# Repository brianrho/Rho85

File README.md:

# Rho85
An Intel 8085 microprocessor trainer

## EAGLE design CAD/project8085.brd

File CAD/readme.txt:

This contains the Eagle .brd and .sch files, as well as PNG images of the schematic and PCB design. 
The schematic has been modified to correct the issues discovered during testing but the PCB design 
is still flawed; yet to be re-routed.

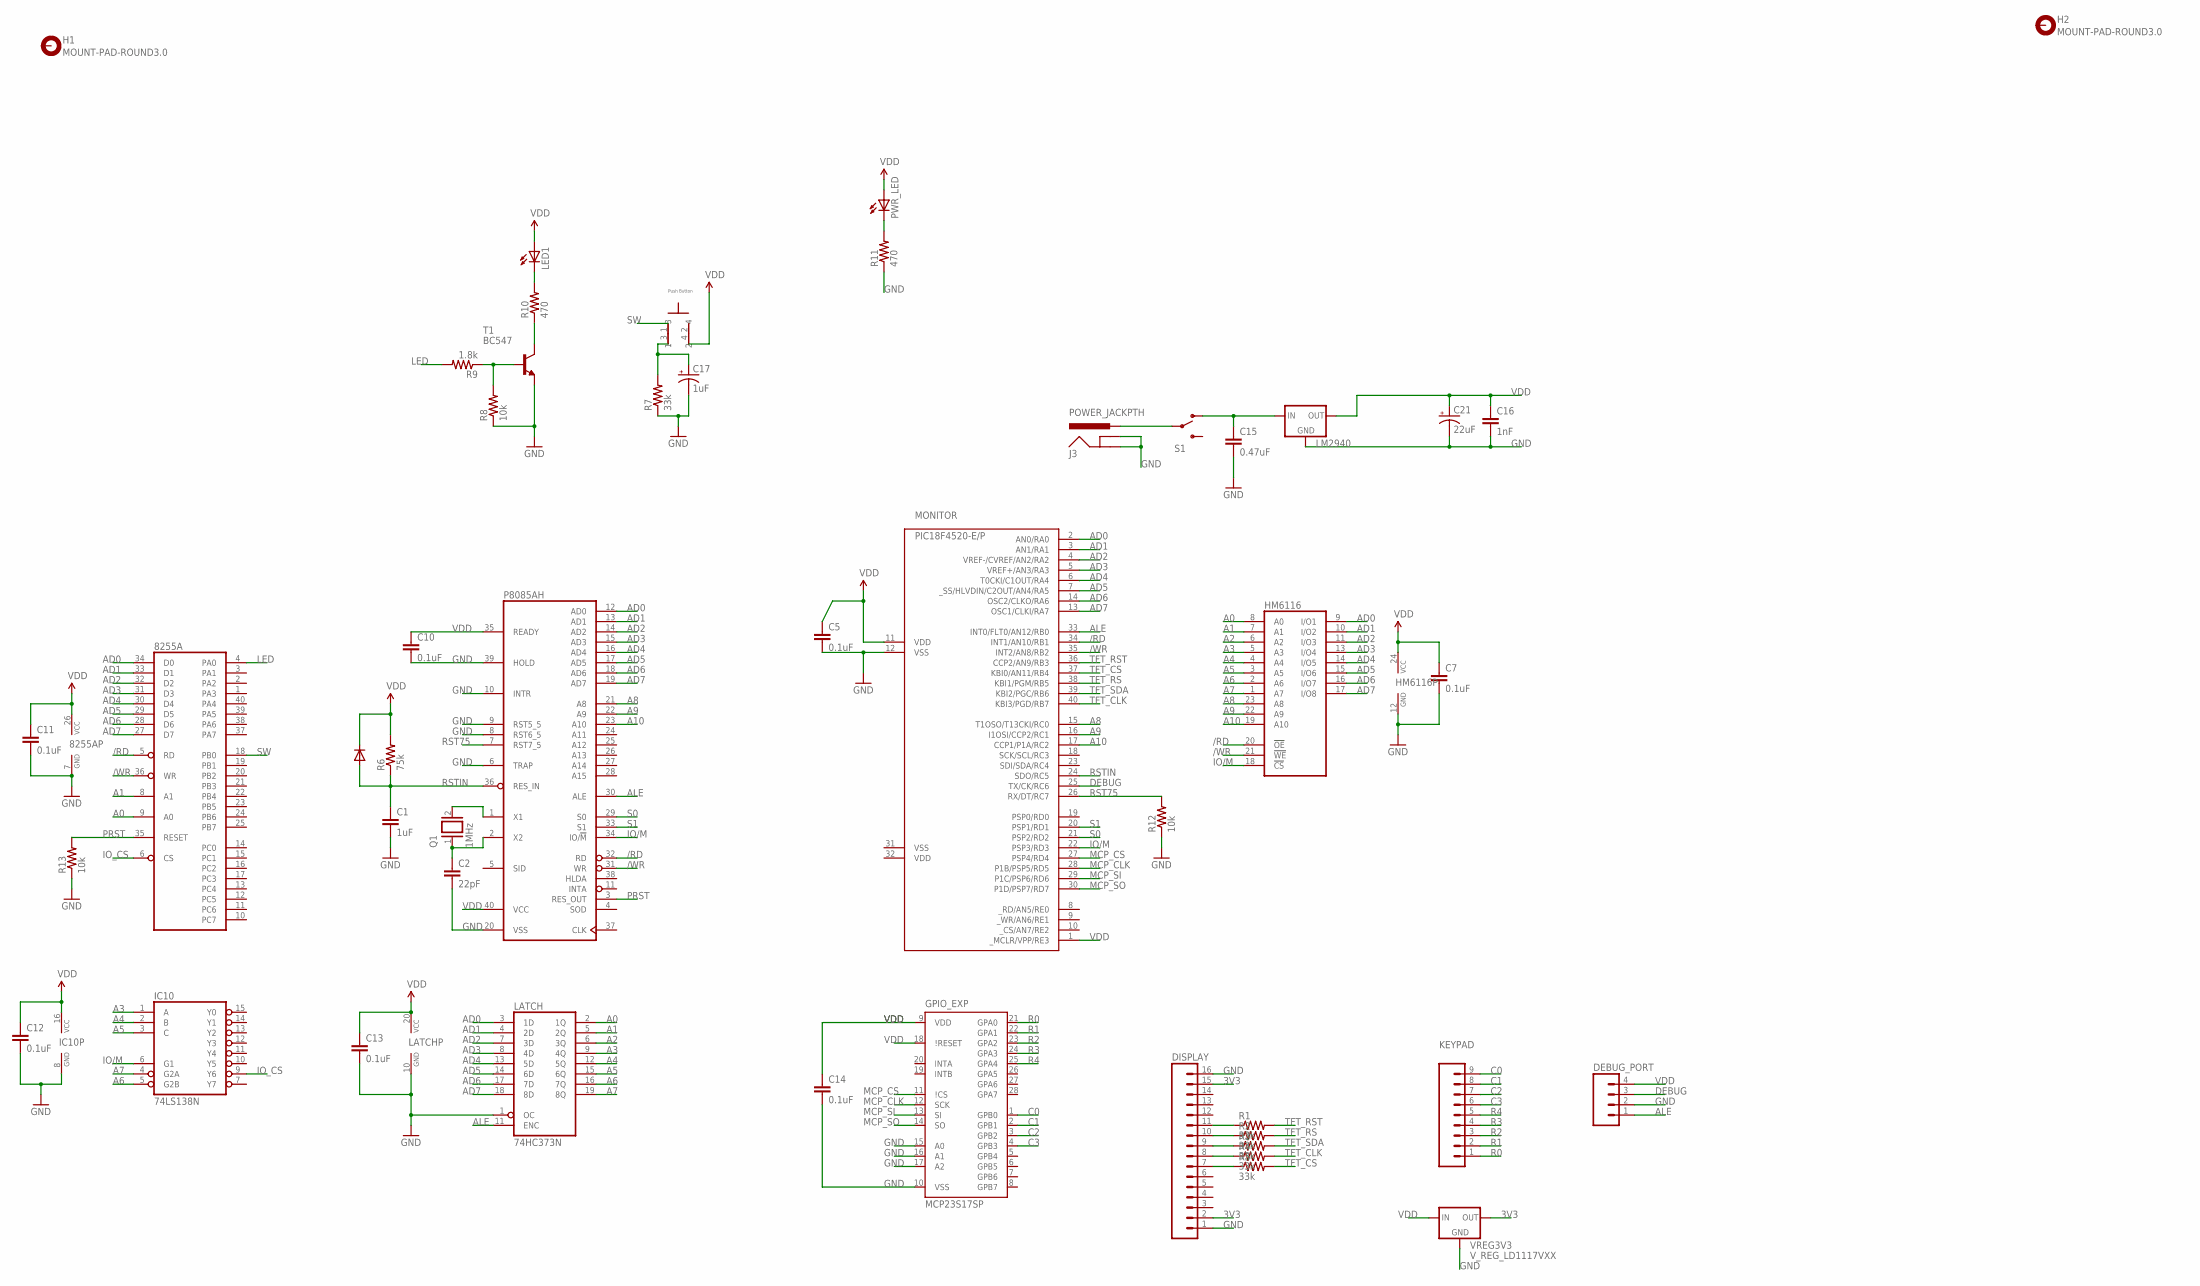
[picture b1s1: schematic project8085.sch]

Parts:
8255A: 8255A; DIL40
C1: 1uF; CAP-PTH-SMALL
C2: 22pF; CAP-PTH-SMALL
C5, C7, C10, C11, C12, C13, C14: 0.1uF; CAP-PTH-SMALL
C15: 0.47uF; CAP-PTH-SMALL
C16: 1nF; CAP-PTH-SMALL
C17: 1uF; CPOL-RADIAL-10UF-25V
C21: 22uF; CPOL-RADIAL-10UF-25V
DEBUG_PORT: M04PTH; 1X04
DISPLAY: M16PTH; 1X16
GPIO_EXP: MCP23S17SP; DIL28-3
H1, H2: MOUNT-PAD-ROUND3.0; 3,0-PAD
HM6116: 6116P; DIL24-6
IC10: 74LS138N; DIL16
IN4148: 1N4148DO35-10; DO35-10
J3: POWER_JACKPTH; POWER_JACK_PTH
KEYPAD: M09; 1X09
LATCH: 74HC373N; DIL20
LED1: LED5MM
LM2940: LM2931T-L; TO220L1
MONITOR: PIC18F4520-E/P; DIL40
P8085AH: 8085; DIL40
PWR_LED: LED5MM
Q1: 1MHz; Q
R1, R2, R3, R4, R5, R7: 33k; AXIAL-0.3
R6: 75k; AXIAL-0.3
R8, R12, R13: 10k; AXIAL-0.3
R9: 1.8k; AXIAL-0.3
R10, R11: 470; AXIAL-0.3
S1: SWITCH-SPDTPTH; SWITCH-SPDT
T1: BC547; TO92
U$3: PUSHBTN
VREG3V3: V_REG_LD1117VXX; 78XXL

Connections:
3V3: DISPLAY.2, DISPLAY.15, VREG3V3.GND (OUT)
/RD: 8255A.5 (RD), HM6116.20 (!OE), MONITOR.34 (INT1/AN10/RB1), P8085AH.32 (RD)
/WR: 8255A.36 (WR), HM6116.21 (!WE), MONITOR.35 (INT2/AN8/RB2), P8085AH.31 (WR)
A0: 8255A.9 (A0), HM6116.8 (A0), LATCH.2 (1Q)
A1: 8255A.8 (A1), HM6116.7 (A1), LATCH.5 (2Q)
A2: HM6116.6 (A2), LATCH.6 (3Q)
A3: HM6116.5 (A3), IC10.1 (A), LATCH.9 (4Q)
A4: HM6116.4 (A4), IC10.2 (B), LATCH.12 (5Q)
A5: HM6116.3 (A5), IC10.3 (C), LATCH.15 (6Q)
A6: HM6116.2 (A6), IC10.5 (G2B), LATCH.16 (7Q)
A7: HM6116.1 (A7), IC10.4 (G2A), LATCH.19 (8Q)
A8: HM6116.23 (A8), MONITOR.15 (T1OSO/T13CKI/RC0), P8085AH.21 (A8)
A9: HM6116.22 (A9), MONITOR.16 (I1OSI/CCP2/RC1), P8085AH.22 (A9)
A10: HM6116.19 (A10), MONITOR.17 (CCP1/P1A/RC2), P8085AH.23 (A10)
AD0: 8255A.34 (D0), HM6116.9 (I/O1), LATCH.3 (1D), MONITOR.2 (AN0/RA0), P8085AH.12 (AD0)
AD1: 8255A.33 (D1), HM6116.10 (I/O2), LATCH.4 (2D), MONITOR.3 (AN1/RA1), P8085AH.13 (AD1)
AD2: 8255A.32 (D2), HM6116.11 (I/O3), LATCH.7 (3D), MONITOR.4 (VREF-/CVREF/AN2/RA2), P8085AH.14 (AD2)
AD3: 8255A.31 (D3), HM6116.13 (I/O4), LATCH.8 (4D), MONITOR.5 (VREF+/AN3/RA3), P8085AH.15 (AD3)
AD4: 8255A.30 (D4), HM6116.14 (I/O5), LATCH.13 (5D), MONITOR.6 (T0CKI/C1OUT/RA4), P8085AH.16 (AD4)
AD5: 8255A.29 (D5), HM6116.15 (I/O6), LATCH.14 (6D), MONITOR.7 (_SS/HLVDIN/C2OUT/AN4/RA5), P8085AH.17 (AD5)
AD6: 8255A.28 (D6), HM6116.16 (I/O7), LATCH.17 (7D), MONITOR.14 (OSC2/CLKO/RA6), P8085AH.18 (AD6)
AD7: 8255A.27 (D7), HM6116.17 (I/O8), LATCH.18 (8D), MONITOR.13 (OSC1/CLKI/RA7), P8085AH.19 (AD7)
ALE: DEBUG_PORT.1, LATCH.11 (ENC), MONITOR.33 (INT0/FLT0/AN12/RB0), P8085AH.30 (ALE)
C0: GPIO_EXP.1 (GPB0), KEYPAD.9
C1: GPIO_EXP.2 (GPB1), KEYPAD.8
C2: GPIO_EXP.3 (GPB2), KEYPAD.7
C3: GPIO_EXP.4 (GPB3), KEYPAD.6
DEBUG: DEBUG_PORT.3, MONITOR.25 (TX/CK/RC6)
GND: 8255A.7 (GND), C1.2, C2.2, C5.2, C7.2, C10.2, C11.2, C12.2, C13.2, C14.2, C15.2, C16.2, C17.2 (-), C21.2 (-), DEBUG_PORT.2, DISPLAY.1, DISPLAY.16, GPIO_EXP.10 (VSS), GPIO_EXP.15 (A0), GPIO_EXP.16 (A1), GPIO_EXP.17 (A2), HM6116.12 (GND), IC10.8 (GND), J3.GND, J3.GNDBREAK, LATCH.1 (OC), LATCH.10 (GND), LM2940.2 (GND), MONITOR.12 (VSS), P8085AH.6 (TRAP), P8085AH.8 (RST6_5), P8085AH.9 (RST5_5), P8085AH.10 (INTR), P8085AH.20 (VSS), P8085AH.39 (HOLD), R7.P$1 (1), R8.P$1 (1), R11.P$1 (1), R12.P$1 (1), R13.P$1 (1), T1.1 (E), VREG3V3.IN (GND)
IO/M: HM6116.18 (!CS), IC10.6 (G1), MONITOR.22 (PSP3/RD3), P8085AH.34 (IO/!M)
IO_CS: 8255A.6 (CS), IC10.9 (Y6)
LED: 8255A.4 (PA0), R9.P$2 (2)
MCP_CLK: GPIO_EXP.12 (SCK), MONITOR.28 (P1B/PSP5/RD5)
MCP_CS: GPIO_EXP.11 (\!CS), MONITOR.27 (PSP4/RD4)
MCP_SI: GPIO_EXP.13 (SI), MONITOR.29 (P1C/PSP6/RD6)
MCP_SO: GPIO_EXP.14 (SO), MONITOR.30 (P1D/PSP7/RD7)
unnamed: R8.P$2 (2), R9.P$1 (1), T1.2 (B)
unnamed: C15.1, LM2940.1 (IN), S1.1 (O)
unnamed: C2.1, P8085AH.2 (X2), Q1.1
unnamed: P8085AH.1 (X1), Q1.2
unnamed: J3.PWR, S1.2
unnamed: DISPLAY.11, R1.P$1 (1)
unnamed: DISPLAY.10, R2.P$1 (1)
unnamed: DISPLAY.9, R3.P$1 (1)
unnamed: DISPLAY.8, R4.P$1 (1)
unnamed: DISPLAY.7, R5.P$1 (1)
unnamed: PWR_LED.K (C), R11.P$2 (2)
unnamed: R10.P$1 (1), T1.3 (C)
unnamed: LED1.K (C), R10.P$2 (2)
PRST: 8255A.35 (RESET), P8085AH.3 (RES_OUT), R13.P$2 (2)
R0: GPIO_EXP.21 (GPA0), KEYPAD.1
R1: GPIO_EXP.22 (GPA1), KEYPAD.2
R2: GPIO_EXP.23 (GPA2), KEYPAD.3
R3: GPIO_EXP.24 (GPA3), KEYPAD.4
R4: GPIO_EXP.25 (GPA4), KEYPAD.5
RST75: MONITOR.26 (RX/DT/RC7), P8085AH.7 (RST7_5), R12.P$2 (2)
RSTIN: C1.1, IN4148.A, MONITOR.24 (SDO/RC5), P8085AH.36 (RES_IN), R6.P$1 (1)
S0: MONITOR.21 (PSP2/RD2), P8085AH.29 (S0)
S1: MONITOR.20 (PSP1/RD1), P8085AH.33 (S1)
SW: 8255A.18 (PB0), U$3.1
SW0: C17.1 (+), R7.P$2 (2), U$3.3
TFT_CLK: MONITOR.40 (KBI3/PGD/RB7), R4.P$2 (2)
TFT_CS: MONITOR.37 (KBI0/AN11/RB4), R5.P$2 (2)
TFT_RS: MONITOR.38 (KBI1/PGM/RB5), R2.P$2 (2)
TFT_RST: MONITOR.36 (CCP2/AN9/RB3), R1.P$2 (2)
TFT_SDA: MONITOR.39 (KBI2/PGC/RB6), R3.P$2 (2)
VDD: 8255A.26 (VCC), C5.1, C7.1, C10.1, C11.1, C12.1, C13.1, C14.1, C16.1, C21.1 (+), DEBUG_PORT.4, GPIO_EXP.9 (VDD), GPIO_EXP.18 (\!RESET), HM6116.24 (VCC), IC10.16 (VCC), IN4148.C, LATCH.20 (VCC), LED1.A, LM2940.3 (OUT), MONITOR.1 (_MCLR/VPP/RE3), MONITOR.11 (VDD), MONITOR.32 (VDD), P8085AH.35 (READY), P8085AH.40 (VCC), PWR_LED.A, R6.P$2 (2), U$3.4, VREG3V3.OUT (IN)
VSS: MONITOR.31 (VSS)

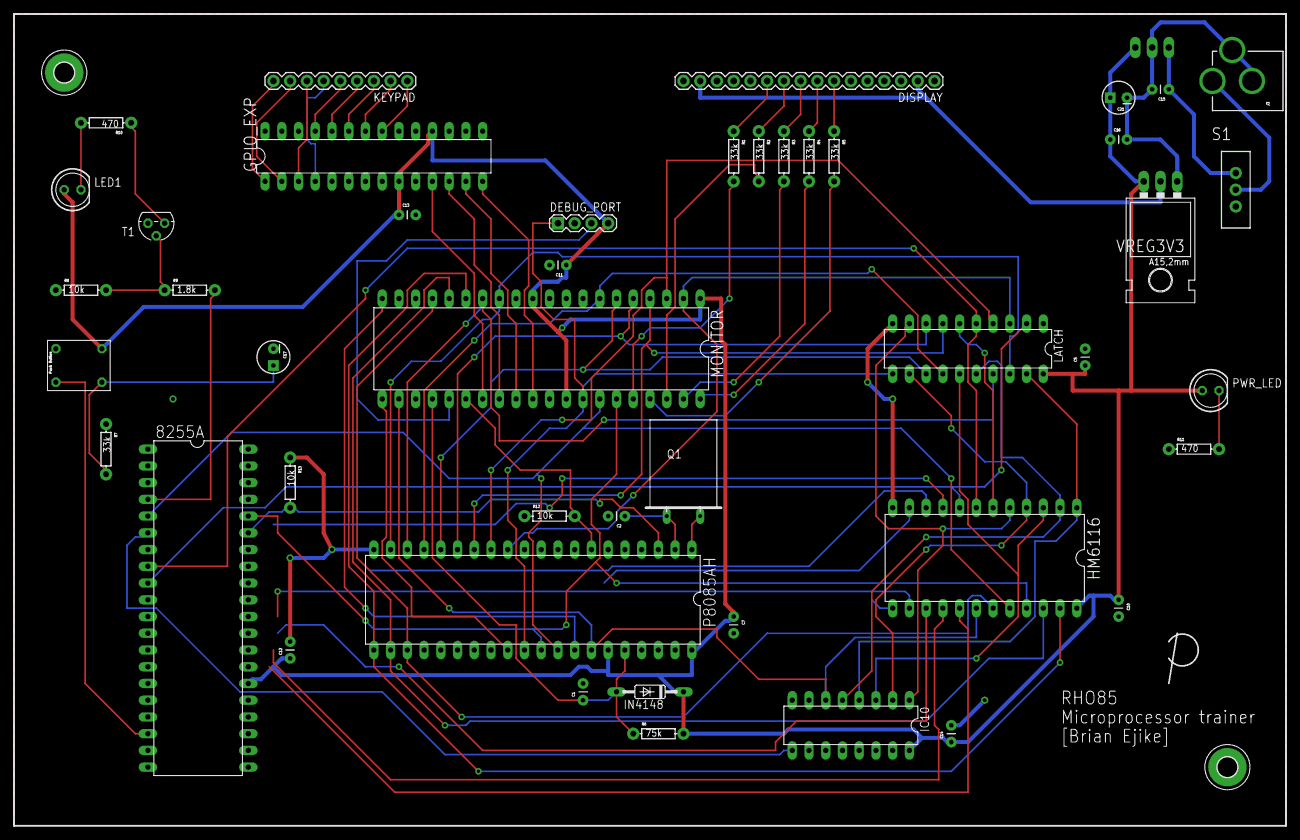
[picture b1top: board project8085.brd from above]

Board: 2 copper layers, 193.0 x 123.2 mm, 48 parts (1 on the bottom side), 67 nets.

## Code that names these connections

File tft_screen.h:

#ifndef TFT_SCREEN_H
#define TFT_SCREEN_H

#include <xc.h>
#include <stdint.h>
#include "utils.h"

#define TFT_CLK_DIR TRISBbits.RB3
#define TFT_CS_DIR TRISBbits.RB6
#define TFT_SDA_DIR TRISBbits.RB5
#define TFT_RST_DIR TRISBbits.RB4
#define TFT_RS_DIR TRISBbits.RB7

#define TFT_CLK LATBbits.LATB3
#define TFT_CS LATBbits.LATB6
#define TFT_SDA LATBbits.LATB5
#define TFT_RST LATBbits.LATB4
#define TFT_RS LATBbits.LATB7

#define ST7735_TFTWIDTH  128
#define ST7735_TFTHEIGHT  160

#define ST7735_NOP     0x00
#define ST7735_SWRESET 0x01
#define ST7735_RDDID   0x04
#define ST7735_RDDST   0x09

#define ST7735_SLPIN   0x10
#define ST7735_SLPOUT  0x11
#define ST7735_PTLON   0x12
#define ST7735_NORON   0x13

#define ST7735_INVOFF  0x20
#define ST7735_INVON   0x21
#define ST7735_DISPOFF 0x28
#define ST7735_DISPON  0x29
#define ST7735_CASET   0x2A
#define ST7735_RASET   0x2B
#define ST7735_RAMWR   0x2C
#define ST7735_RAMRD   0x2E

#define ST7735_PTLAR   0x30
#define ST7735_COLMOD  0x3A
#define ST7735_MADCTL  0x36

#define ST7735_FRMCTR1 0xB1
#define ST7735_FRMCTR2 0xB2
#define ST7735_FRMCTR3 0xB3
#define ST7735_INVCTR  0xB4
#define ST7735_DISSET5 0xB6

#define ST7735_PWCTR1  0xC0
#define ST7735_PWCTR2  0xC1
#define ST7735_PWCTR3  0xC2
#define ST7735_PWCTR4  0xC3
#define ST7735_PWCTR5  0xC4
#define ST7735_VMCTR1  0xC5

#define ST7735_RDID1   0xDA
#define ST7735_RDID2   0xDB
#define ST7735_RDID3   0xDC
#define ST7735_RDID4   0xDD

#define ST7735_PWCTR6  0xFC

#define ST7735_GMCTRP1 0xE0
#define ST7735_GMCTRN1 0xE1

// Color definitions
#define	ST7735_BLACK   0x0000
#define	ST7735_RED     0x001F
#define	ST7735_BLUE    0xF800
#define	ST7735_GREEN   0x07E0
#define ST7735_CYAN    0x07FF
#define ST7735_MAGENTA 0xF81F
#define ST7735_YELLOW  0xFFE0
#define ST7735_WHITE   0xFFFF

void init_screen(void);
void set_window(uint8_t x0, uint8_t y0, uint8_t x1, uint8_t y1);
void push_color(uint16_t color);
void fill_screen(uint16_t color);
void draw_pixel(int16_t x, int16_t y, uint16_t color);
void draw_vline(int16_t x, int16_t y, int16_t h, uint16_t color);
void draw_hline(int16_t x, int16_t y, int16_t w, uint16_t color);
void draw_rect(int16_t x, int16_t y, int16_t w, int16_t h, uint16_t color);
void fill_rect(int16_t x, int16_t y, int16_t w, int16_t h, uint16_t color);
void draw_round_rect(int16_t x, int16_t y, int16_t w, int16_t h, int16_t r, uint16_t color);
void writech(uint8_t c);
void draw_char(int16_t x, int16_t y, unsigned char c, uint16_t color, uint8_t size);
void draw_bitmap(int16_t x, int16_t y, const uint8_t *bitmap, int16_t w, int16_t h, uint16_t color);
void set_rotation(uint8_t r);
void set_cursor(int16_t x, int16_t y);
void set_text_color(uint16_t c);
uint16_t color_565(uint8_t r, uint8_t g, uint8_t b);
void set_text_size(uint8_t s);

#endif

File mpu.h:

/* 
 * File:   mpu.h
 * Author: Brian Rho
 *
 * Created on 01 June 2016, 00:08
 */

#include "ram_mem.h"

// PIC-8085 control pins
#define RESET_IN_DIR    TRISCbits.RC5
#define STAT0_DIR   TRISDbits.RD1
#define STAT1_DIR   TRISDbits.RD2
#define RST75_DIR   TRISCbits.RC7

#define RESET_IN    LATCbits.LATC5
#define STAT0   PORTDbits.RD2
#define STAT1   PORTDbits.RD3
#define RST75   LATCbits.LATC7

// some 8085 instructions
#define JUMP    0xC3

#define MOVB    0x78
#define MOVC    0x79
#define MOVD    0x7A
#define MOVE    0x7B
#define MOVH    0x7C
#define MOVL    0x7D

#define STA     0x32
#define NOOP     0x00
#define SPHL    0xF9
#define MVIH    0x26
#define MVIL    0x2E

#define NUM_REGS    10

void init_mpu_interface(void);
void reset_mpu(void);
void halt_mpu(void);
void start_mpu(unsigned int addr);

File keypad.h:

#ifndef KEYPAD_H
#define KEYPAD_H

#include <xc.h>

#define _XTAL_FREQ  32000000

#define MCP_MOSI_DIR    TRISDbits.RD6
#define MCP_MISO_DIR    TRISDbits.RD7
#define MCP_SCK_DIR     TRISDbits.RD5
#define MCP_CS_DIR      TRISDbits.RD4

#define MCP_MOSI        LATDbits.LATD6
#define MCP_MISO        PORTDbits.RD7
#define MCP_SCK         LATDbits.LATD5
#define MCP_CS          LATDbits.LATD4

enum {
    IODIRA,     IODIRB,
    IPOLA,      IPOLB,
    GPINTENA,   GPINTENB,
    DEFVALA,    DEFVALB,
    INTCONA,    INTCONB,
    IOCONA,     IOCONB,
    GPPUA,      GPPUB,
    INTFA,      INTFB,
    INTCAPA,    INTCAPB,
    GPIOA,      GPIOB,
    OLATA,      OLATB
};

unsigned char regs[22];

void init_keypad();
char scan_keypad();
void read_all();

#endif

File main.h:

#ifndef MAIN_H
#define MAIN_H

#include <xc.h>

#define LSB_PORT	PORTA
#define LSB_PORT_LAT	LATA
#define LSB_PORT_DIR	TRISA

#define MSB_PORT	PORTC
#define MSB_PORT_LAT	LATC
#define	MSB_PORT_DIR	TRISC

// Octal latch
#define ALE     PORTBbits.RB0
#define ALE_LAT LATBbits.LATB0
#define ALE_DIR TRISBbits.RB0

// RAM
#define IOM      PORTDbits.RD3
#define IOM_LAT  LATDbits.LATD3
#define IOM_DIR  TRISDbits.RD3

#define RD      PORTBbits.RB1
#define RD_LAT  LATBbits.LATB1
#define RD_DIR  TRISBbits.RB1

#define WR      PORTBbits.RB2
#define WR_LAT  LATBbits.LATB2
#define WR_DIR  TRISBbits.RB2

#define MEM_SIZE    2048
#define MEM_MAX     MEM_SIZE - 1
#define MEM_MIN     0x50

const unsigned char logo[] = {
    0xff,0xff,0xff,0xff,0xff,0xff,0xff,0xff,0xff,0xff,0xff,0xff,0xff,0xff,
    0xff,0xff,0xff,0xff,0xff,0xff,0xff,0xff,0xff,0xff,0xff,0xff,0xff,0xff,
    0xff,0xff,0xff,0xff,0xef,0xff,0xff,0xff,0xff,0xff,0xff,0xff,0xff,0xff,
    0xff,0xff,0xff,0xff,0xe7,0xff,0xff,0xff,0xff,0xff,0xff,0xff,0xff,0xff,
    0xff,0xff,0xff,0xff,0xe7,0xff,0xff,0xff,0xff,0xff,0xff,0xff,0xff,0xff,
    0xff,0xff,0xff,0xff,0xcf,0xff,0xff,0xff,0xff,0xc0,0xff,0xff,0xff,0xff,
    0xff,0xff,0xff,0xff,0xcf,0xff,0xff,0xff,0xfe,0x6,0x3f,0xff,0xe0,0xf,
    0xfe,0x0,0x1f,0xff,0xcf,0xff,0xff,0xff,0xf8,0x3,0x9f,0x80,0xf,0xff,
    0xf0,0x1f,0x81,0xff,0xcf,0xff,0xff,0xff,0xf1,0xff,0x9f,0xcf,0xff,0xff,
    0xfe,0x7f,0xf8,0x7f,0x9f,0xff,0xfe,0x3f,0xe7,0xff,0x9f,0x9f,0xff,0xff,
    0xfe,0x7f,0xfc,0x7f,0x9f,0x8f,0xfc,0xf,0xcf,0xff,0x3f,0x3f,0xff,0xff,
    0xfc,0x7f,0xfe,0x7f,0x9e,0xf,0xf8,0xcf,0x8f,0xfc,0x7e,0x3f,0xff,0xff,
    0xfc,0xff,0xfc,0xff,0x3c,0xcf,0xf1,0xc7,0xcf,0xf9,0xfc,0x7f,0xff,0xff,
    0xfc,0xff,0xe1,0xff,0x39,0xcf,0xe7,0xe7,0xcf,0xe3,0xf8,0x1,0xff,0xff,
    0xf8,0x1c,0xf,0xff,0x73,0xcf,0xc7,0xe7,0xef,0x9f,0xf0,0x7c,0x3f,0xff,
    0xf8,0x1,0xff,0xfe,0x67,0xdf,0xcf,0xef,0xe6,0x3f,0xff,0xff,0x1f,0xff,
    0xf9,0x8f,0xff,0xfe,0xcf,0x9f,0x9f,0xcf,0xf0,0xff,0xff,0xff,0x9f,0xff,
    0xf3,0xc7,0xff,0xfc,0x8f,0x9f,0xbf,0xcf,0xe0,0xff,0xff,0xff,0x9f,0xff,
    0xf3,0xe3,0xff,0xfc,0x1f,0x3f,0x3f,0x9f,0xce,0x7f,0xff,0xff,0x3f,0xff,
    0xf3,0xf3,0xff,0xf8,0x3f,0x3e,0x7f,0xbf,0x1f,0x3f,0x7f,0xfe,0x7f,0xff,
    0xe7,0xf1,0xff,0xf8,0x7f,0x3e,0x7f,0x7e,0x7f,0xbf,0x7f,0xfc,0xff,0xff,
    0xe7,0xf8,0xff,0xf8,0xfe,0x7e,0xfc,0xfc,0xff,0xde,0x7f,0xf9,0xff,0xff,
    0xe7,0xfc,0x3f,0x11,0xfe,0x7c,0xf9,0xfc,0xff,0x9e,0x3f,0xe3,0xff,0xff,
    0xcf,0xff,0x80,0xf3,0xfe,0x7c,0xe3,0xfc,0x7f,0x3f,0x86,0xf,0xff,0xff,
    0xff,0xff,0xff,0xff,0xfe,0x7c,0xf,0xff,0x0,0x7f,0xf0,0xff,0xff,0xff,
    0xff,0xff,0xff,0xff,0xff,0xff,0xff,0xff,0xff,0xff,0xff,0xff,0xff,0xff,
    0xff,0xff,0xff,0xff,0xff,0xff,0xff,0xff,0xff,0xff,0xff,0xff,0xff,0xff,
    0xff,0xff,0xff,0xff,0xff,0xff,0xff,0xff,0xff,0xff,0xff,0xff,0xff,0xff,
    0xff,0xff,0xff,0xff,0xff,0xff,0xff,0xff,0xff,0xff,0xff,0xff,0xff,0xff
};

#endif

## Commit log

2016-12-14 Added project report
2016-12-14 Added .hex file
2016-12-26 Modified project report
2016-12-26 Uploaded CAD files
2024-01-12 Add missing mpu files

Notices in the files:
parts and their libraries:
SparkFun-Connectors: Licensing: Creative Commons ShareAlike 4.0 International - https://creativecommons.org/licenses/by-sa/4.0
